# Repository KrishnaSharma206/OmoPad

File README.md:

# OmoPad
OmoPad is custom macropad with 9 MX switches, One rotary encoder and an OLED display.
It uses a KMK firmware, the rotary encoder provides volume control.
It has 9 SK6812 mini LEDs, which can be customised.

# CAD Model
It uses 4x M3 screws to assemble, there are two 3D printed parts.

# PCB

Schematic

PCB Design

# Firmware Overview

I am using KMK for thte firmware

# BOM

1. 1x SEEED XIAO RP2040
2. 4x M3 screws
3. 4x M3 bolts
4. 9x MX switches
5. 9x MX key caps
6. 1x EC11 encoder with knob
7. 1x SD1306 128x32 OLED display

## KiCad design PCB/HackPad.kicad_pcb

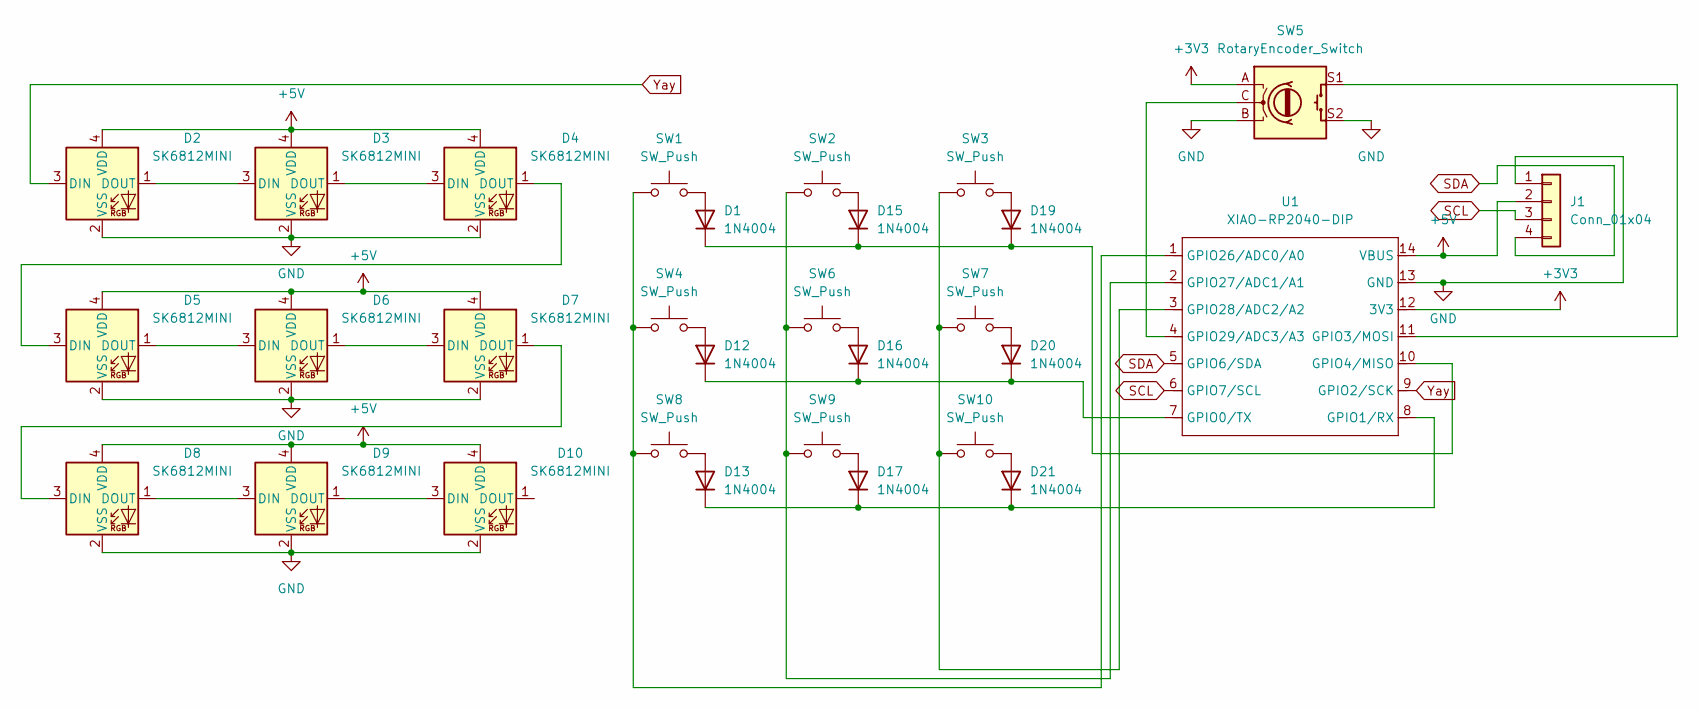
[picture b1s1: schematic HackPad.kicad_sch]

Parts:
D1, D12, D13, D15, D16, D17, D19, D20, D21: 1N4004; D_DO-41_SOD81_P10.16mm_Horizontal
D2, D3, D4, D5, D6, D7, D8, D9, D10: SK6812MINI; LED_SK6812MINI_PLCC4_3.5x3.5mm_P1.75mm
J1: Conn_01x04; SSD1306-0.91-OLED-4pin-128x32
SW1, SW2, SW3, SW4, SW6, SW7, SW8, SW9, SW10: SW_Push; SW_Cherry_MX_1.00u_PCB
SW5: RotaryEncoder_Switch; RotaryEncoder_Alps_EC11E-Switch_Vertical_H20mm
U1: XIAO-RP2040-DIP

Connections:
+3V3: SW5.A, U1.12 (3V3)
+5V: D2.4 (VDD), D3.4 (VDD), D4.4 (VDD), D5.4 (VDD), D6.4 (VDD), D7.4 (VDD), D8.4 (VDD), D9.4 (VDD), D10.4 (VDD), J1.2, U1.14 (VBUS)
GND: D2.2 (VSS), D3.2 (VSS), D4.2 (VSS), D5.2 (VSS), D6.2 (VSS), D7.2 (VSS), D8.2 (VSS), D9.2 (VSS), D10.2 (VSS), J1.1, SW5.B, SW5.S2, U1.13 (GND)
unnamed: D1.2 (A), SW1.2
unnamed: D1.1 (K), D15.1 (K), D19.1 (K), U1.10 (GPIO4/MISO)
unnamed: D2.1 (DOUT), D3.3 (DIN)
unnamed: D3.1 (DOUT), D4.3 (DIN)
unnamed: D4.1 (DOUT), D5.3 (DIN)
unnamed: D5.1 (DOUT), D6.3 (DIN)
unnamed: D6.1 (DOUT), D7.3 (DIN)
unnamed: D7.1 (DOUT), D8.3 (DIN)
unnamed: D8.1 (DOUT), D9.3 (DIN)
unnamed: D9.1 (DOUT), D10.3 (DIN)
unnamed: D12.2 (A), SW4.2
unnamed: D12.1 (K), D16.1 (K), D20.1 (K), U1.7 (GPIO0/TX)
unnamed: D13.2 (A), SW8.2
unnamed: D13.1 (K), D17.1 (K), D21.1 (K), U1.8 (GPIO1/RX)
unnamed: D15.2 (A), SW2.2
unnamed: D16.2 (A), SW6.2
unnamed: D17.2 (A), SW9.2
unnamed: D19.2 (A), SW3.2
unnamed: D20.2 (A), SW7.2
unnamed: D21.2 (A), SW10.2
unnamed: SW5.S1, U1.11 (GPIO3/MOSI)
unnamed: SW1.1, SW4.1, SW8.1, U1.1 (GPIO26/ADC0/A0)
unnamed: SW2.1, SW6.1, SW9.1, U1.2 (GPIO27/ADC1/A1)
unnamed: SW3.1, SW7.1, SW10.1, U1.3 (GPIO28/ADC2/A2)
unnamed: SW5.C, U1.4 (GPIO29/ADC3/A3)
SCL: J1.3, U1.6 (GPIO7/SCL)
SDA: J1.4, U1.5 (GPIO6/SDA)
Yay: D2.3 (DIN), U1.9 (GPIO2/SCK)

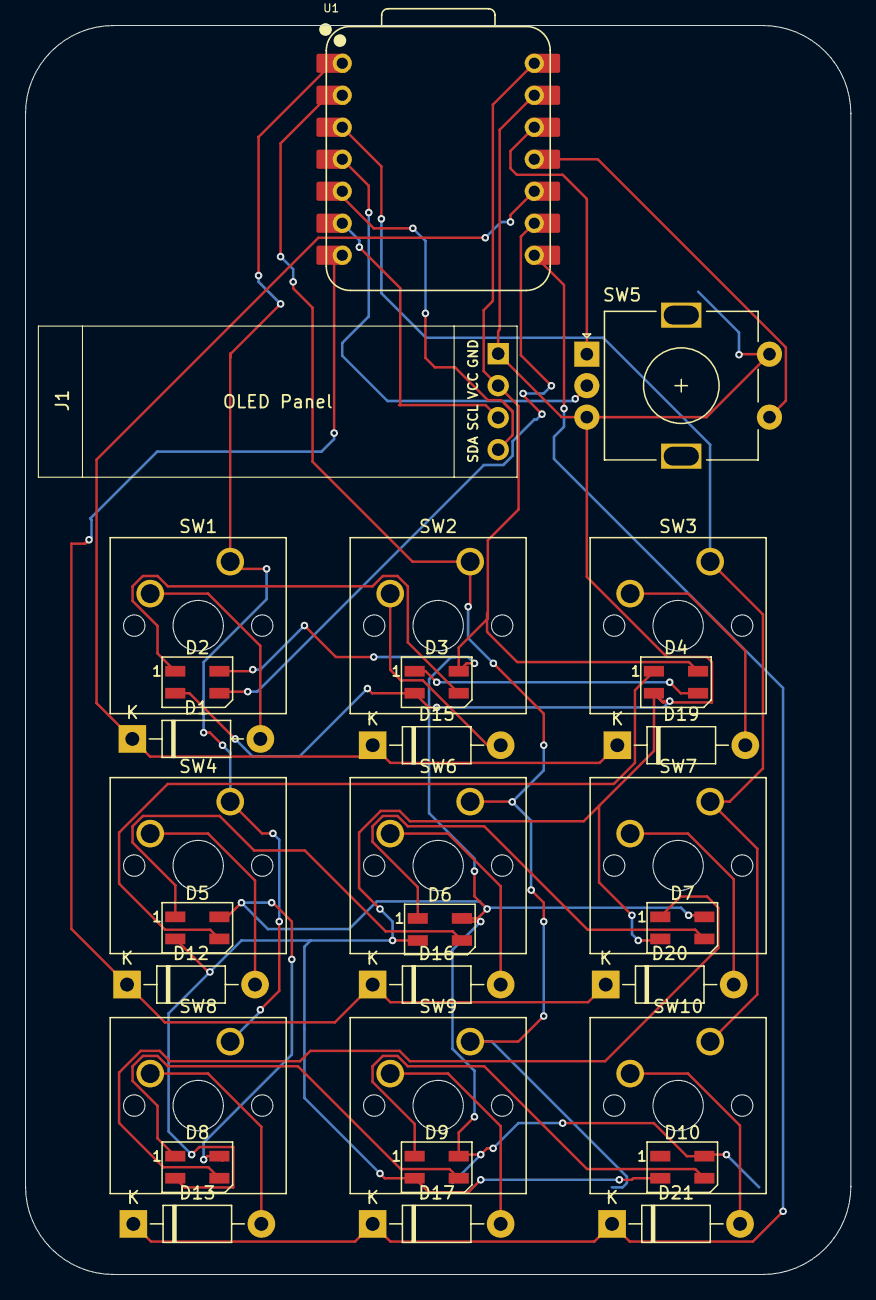
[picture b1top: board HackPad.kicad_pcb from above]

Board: 2 copper layers, 65.5 x 99.2 mm, 30 parts (0 on the bottom side), 31 nets.

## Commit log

2025-05-29 Create example
